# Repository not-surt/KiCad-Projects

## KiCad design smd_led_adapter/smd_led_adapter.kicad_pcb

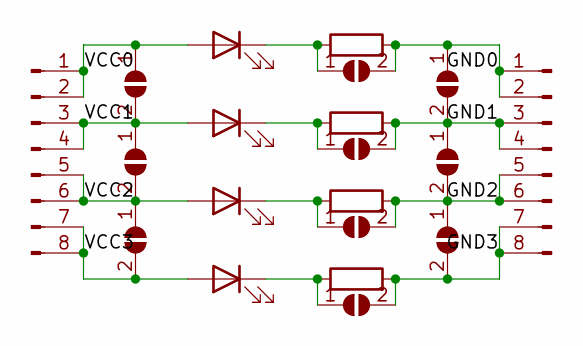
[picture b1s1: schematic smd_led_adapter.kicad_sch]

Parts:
D1, D2, D3, D4: LED; 1210_to_0603_combo_HandSolder
J1, J2: Conn_01x08_Male; PinHeader_1x08_P2.54mm_Vertical
JP1, JP2, JP3, JP4, JP5, JP6, JP7, JP8, JP9, JP10: SolderJumper_2_Open; SolderJumper-2_P1.3mm_Open_RoundedPad1.0x1.5mm
R1, R2, R3, R4: R; R_1206_3216Metric_Pad1.30x1.75mm_HandSolder

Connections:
/GND0: J2.1, J2.2, JP4.2 (B), JP8.1 (A), R1.2
/GND1: J2.3, J2.4, JP5.2 (B), JP8.2 (B), JP9.1 (A), R2.2
/GND2: J2.5, J2.6, JP6.2 (B), JP9.2 (B), JP10.1 (A), R3.2
/GND3: J2.7, J2.8, JP7.2 (B), JP10.2 (B), R4.2
/VCC0: D1.2 (A), J1.1, J1.2, JP1.1 (A)
/VCC1: D2.2 (A), J1.3, J1.4, JP1.2 (B), JP2.1 (A)
/VCC2: D3.2 (A), J1.5, J1.6, JP2.2 (B), JP3.1 (A)
/VCC3: D4.2 (A), J1.7, J1.8, JP3.2 (B)
unnamed: D1.1 (K), JP4.1 (A), R1.1
unnamed: D2.1 (K), JP5.1 (A), R2.1
unnamed: D3.1 (K), JP6.1 (A), R3.1
unnamed: D4.1 (K), JP7.1 (A), R4.1

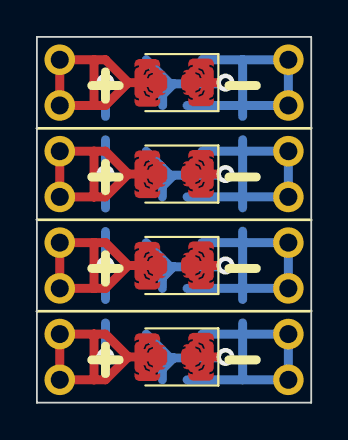
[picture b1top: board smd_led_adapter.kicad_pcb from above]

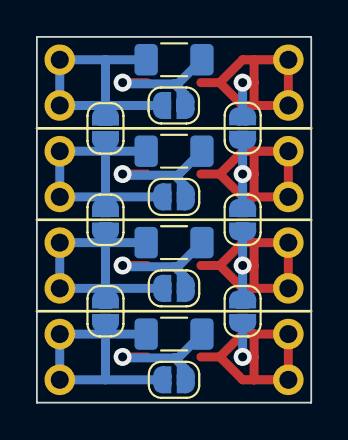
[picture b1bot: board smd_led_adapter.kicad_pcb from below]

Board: 2 copper layers, 15.2 x 20.3 mm, 20 parts (16 on the bottom side), 12 nets.

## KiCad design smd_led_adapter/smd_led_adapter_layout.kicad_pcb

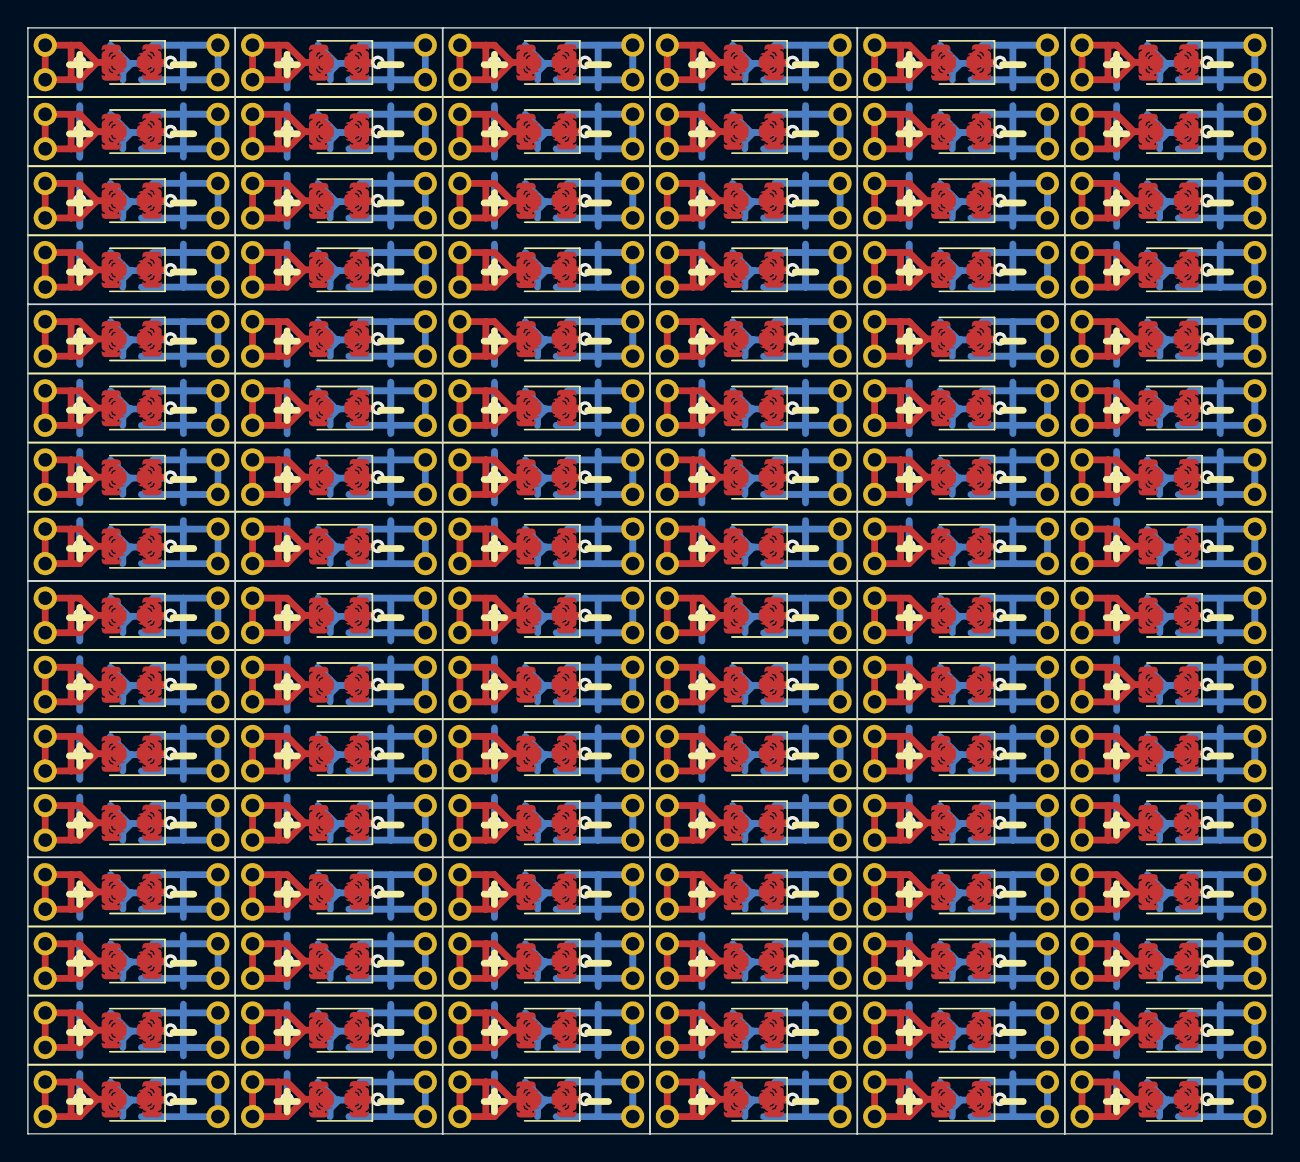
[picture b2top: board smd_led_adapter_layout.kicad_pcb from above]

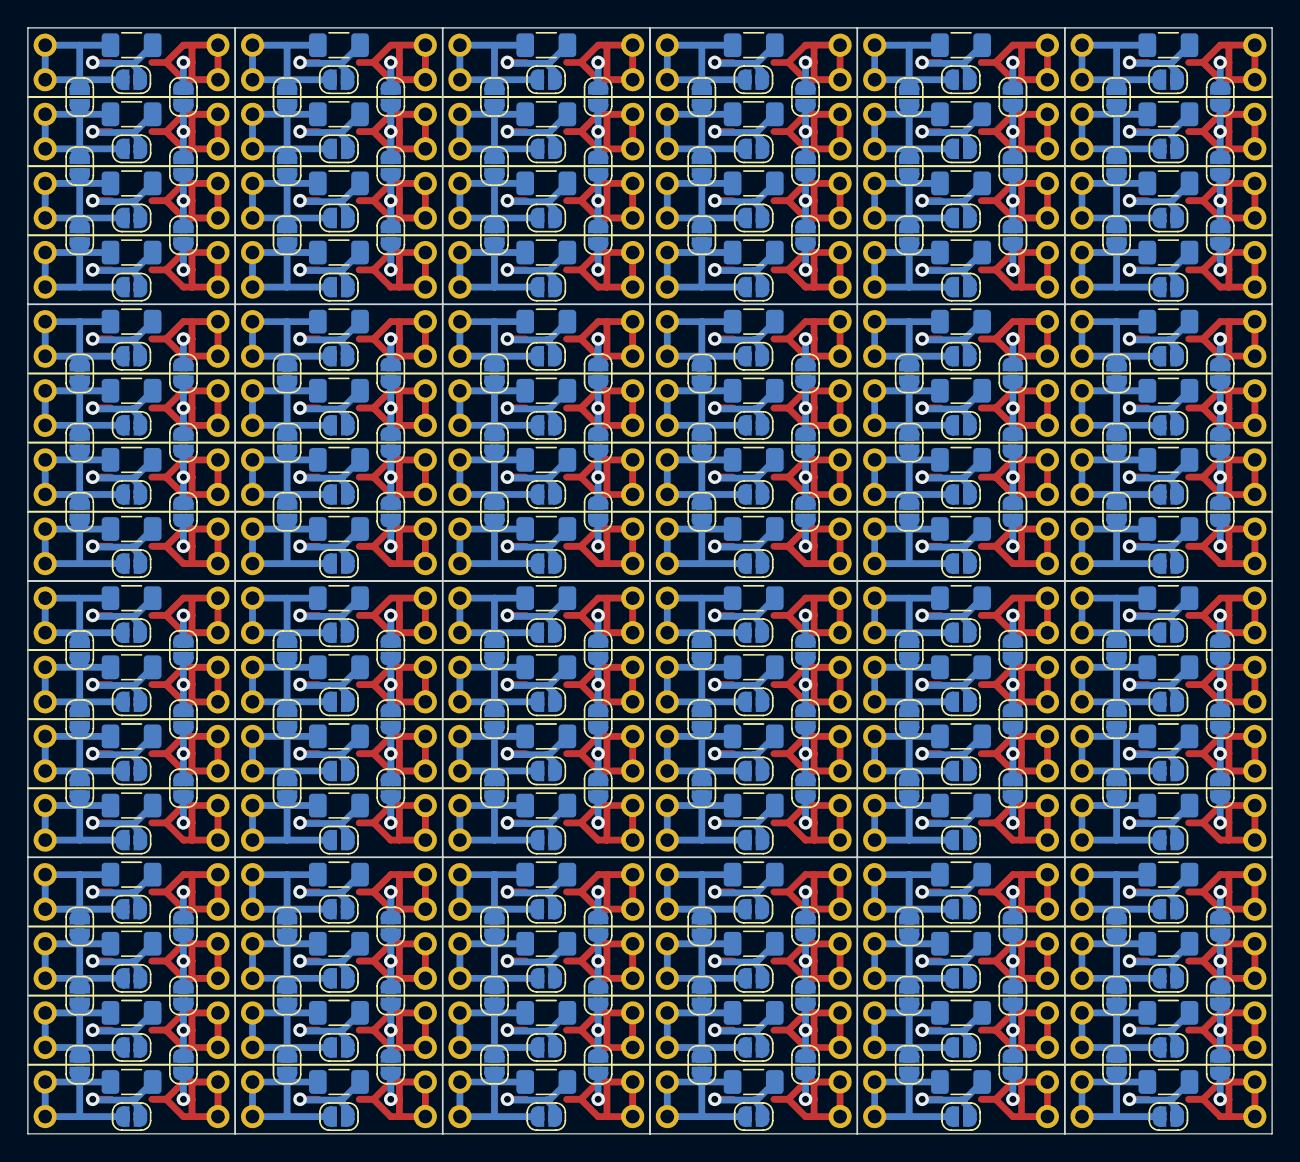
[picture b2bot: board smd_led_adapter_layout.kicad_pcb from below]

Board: 2 copper layers, 91.4 x 81.3 mm, 480 parts (384 on the bottom side), 12 nets.

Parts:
D1, D2, D3, D4, D5, D6, D7, D8, D9, D10, D11, D12, D13, D14, D15, D16, D17, D18, D19, D20, D21, D22, D23, D24, D25, D26, D27, D28, D29, D30, D31, D32, D33, D34, D35, D36, D37, D38, D39, D40, D41, D42, D43, D44, D45, D46, D47, D48, D49, D50, D51, D52, D53, D54, D55, D56, D57, D58, D59, D60, D61, D62, D63, D64, D65, D66, D67, D68, D69, D70, D71, D72, D73, D74, D75, D76, D77, D78, D79, D80, D81, D82, D83, D84, D85, D86, D87, D88, D89, D90, D91, D92, D93, D94, D95, D96: LED; 1210_to_0603_combo_HandSolder
J1, J2, J3, J4, J5, J6, J7, J8, J9, J10, J11, J12, J13, J14, J15, J16, J17, J18, J19, J20, J21, J22, J23, J24, J25, J26, J27, J28, J29, J30, J31, J32, J33, J34, J35, J36, J37, J38, J39, J40, J41, J42, J43, J44, J45, J46, J47, J48: Conn_01x08_Male; PinHeader_1x08_P2.54mm_Vertical
JP1, JP2, JP3, JP4, JP5, JP6, JP7, JP8, JP9, JP10, JP11, JP12, JP13, JP14, JP15, JP16, JP17, JP18, JP19, JP20, JP21, JP22, JP23, JP24, JP25, JP26, JP27, JP28, JP29, JP30, JP31, JP32, JP33, JP34, JP35, JP36, JP37, JP38, JP39, JP40, JP41, JP42, JP43, JP44, JP45, JP46, JP47, JP48, JP49, JP50, JP51, JP52, JP53, JP54, JP55, JP56, JP57, JP58, JP59, JP60, JP61, JP62, JP63, JP64, JP65, JP66, JP67, JP68, JP69, JP70, JP71, JP72, JP73, JP74, JP75, JP76, JP77, JP78, JP79, JP80, JP81, JP82, JP83, JP84, JP85, JP86, JP87, JP88, JP89, JP90, JP91, JP92, JP93, JP94, JP95, JP96, JP97, JP98, JP99, JP100, JP101, JP102, JP103, JP104, JP105, JP106, JP107, JP108, JP109, JP110, JP111, JP112, JP113, JP114, JP115, JP116, JP117, JP118, JP119, JP120, JP121, JP122, JP123, JP124, JP125, JP126, JP127, JP128, JP129, JP130, JP131, JP132, JP133, JP134, JP135, JP136, JP137, JP138, JP139, JP140, JP141, JP142, JP143, JP144, JP145, JP146, JP147, JP148, JP149, JP150, JP151, JP152, JP153, JP154, JP155, JP156, JP157, JP158, JP159, JP160, JP161, JP162, JP163, JP164, JP165, JP166, JP167, JP168, JP169, JP170, JP171, JP172, JP173, JP174, JP175, JP176, JP177, JP178, JP179, JP180, JP181, JP182, JP183, JP184, JP185, JP186, JP187, JP188, JP189, JP190, JP191, JP192, JP193, JP194, JP195, JP196, JP197, JP198, JP199, JP200, JP201, JP202, JP203, JP204, JP205, JP206, JP207, JP208, JP209, JP210, JP211, JP212, JP213, JP214, JP215, JP216, JP217, JP218, JP219, JP220, JP221, JP222, JP223, JP224, JP225, JP226, JP227, JP228, JP229, JP230, JP231, JP232, JP233, JP234, JP235, JP236, JP237, JP238, JP239, JP240: SolderJumper_2_Open; SolderJumper-2_P1.3mm_Open_RoundedPad1.0x1.5mm
R1, R2, R3, R4, R5, R6, R7, R8, R9, R10, R11, R12, R13, R14, R15, R16, R17, R18, R19, R20, R21, R22, R23, R24, R25, R26, R27, R28, R29, R30, R31, R32, R33, R34, R35, R36, R37, R38, R39, R40, R41, R42, R43, R44, R45, R46, R47, R48, R49, R50, R51, R52, R53, R54, R55, R56, R57, R58, R59, R60, R61, R62, R63, R64, R65, R66, R67, R68, R69, R70, R71, R72, R73, R74, R75, R76, R77, R78, R79, R80, R81, R82, R83, R84, R85, R86, R87, R88, R89, R90, R91, R92, R93, R94, R95, R96: R; R_1206_3216Metric_Pad1.30x1.75mm_HandSolder

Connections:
/GND0: J2.1, J2.2, J4.1, J4.2, J6.1, J6.2, J8.1, J8.2, J10.1, J10.2, J12.1, J12.2, J14.1, J14.2, J16.1, J16.2, J18.1, J18.2, J20.1, J20.2, J22.1, J22.2, J24.1, J24.2, J26.1, J26.2, J28.1, J28.2, J30.1, J30.2, J32.1, J32.2, J34.1, J34.2, J36.1, J36.2, J38.1, J38.2, J40.1, J40.2, J42.1, J42.2, J44.1, J44.2, J46.1, J46.2, J48.1, J48.2, JP4.2 (B), JP8.1 (A), JP14.2 (B), JP18.1 (A), JP24.2 (B), JP28.1 (A), JP34.2 (B), JP38.1 (A), JP44.2 (B), JP48.1 (A), JP54.2 (B), JP58.1 (A), JP64.2 (B), JP68.1 (A), JP74.2 (B), JP78.1 (A), JP84.2 (B), JP88.1 (A), JP94.2 (B), JP98.1 (A), JP104.2 (B), JP108.1 (A), JP114.2 (B), JP118.1 (A), JP124.2 (B), JP128.1 (A), JP134.2 (B), JP138.1 (A), JP144.2 (B), JP148.1 (A), JP154.2 (B), JP158.1 (A), JP164.2 (B), JP168.1 (A), JP174.2 (B), JP178.1 (A), JP184.2 (B), JP188.1 (A), JP194.2 (B), JP198.1 (A), JP204.2 (B), JP208.1 (A), JP214.2 (B), JP218.1 (A), JP224.2 (B), JP228.1 (A), JP234.2 (B), JP238.1 (A), R1.2, R5.2, R9.2, R13.2, R17.2, R21.2, R25.2, R29.2, R33.2, R37.2, R41.2, R45.2, R49.2, R53.2, R57.2, R61.2, R65.2, R69.2, R73.2, R77.2, R81.2, R85.2, R89.2, R93.2
/GND1: J2.3, J2.4, J4.3, J4.4, J6.3, J6.4, J8.3, J8.4, J10.3, J10.4, J12.3, J12.4, J14.3, J14.4, J16.3, J16.4, J18.3, J18.4, J20.3, J20.4, J22.3, J22.4, J24.3, J24.4, J26.3, J26.4, J28.3, J28.4, J30.3, J30.4, J32.3, J32.4, J34.3, J34.4, J36.3, J36.4, J38.3, J38.4, J40.3, J40.4, J42.3, J42.4, J44.3, J44.4, J46.3, J46.4, J48.3, J48.4, JP5.2 (B), JP8.2 (B), JP9.1 (A), JP15.2 (B), JP18.2 (B), JP19.1 (A), JP25.2 (B), JP28.2 (B), JP29.1 (A), JP35.2 (B), JP38.2 (B), JP39.1 (A), JP45.2 (B), JP48.2 (B), JP49.1 (A), JP55.2 (B), JP58.2 (B), JP59.1 (A), JP65.2 (B), JP68.2 (B), JP69.1 (A), JP75.2 (B), JP78.2 (B), JP79.1 (A), JP85.2 (B), JP88.2 (B), JP89.1 (A), JP95.2 (B), JP98.2 (B), JP99.1 (A), JP105.2 (B), JP108.2 (B), JP109.1 (A), JP115.2 (B), JP118.2 (B), JP119.1 (A), JP125.2 (B), JP128.2 (B), JP129.1 (A), JP135.2 (B), JP138.2 (B), JP139.1 (A), JP145.2 (B), JP148.2 (B), JP149.1 (A), JP155.2 (B), JP158.2 (B), JP159.1 (A), JP165.2 (B), JP168.2 (B), JP169.1 (A), JP175.2 (B), JP178.2 (B), JP179.1 (A), JP185.2 (B), JP188.2 (B), JP189.1 (A), JP195.2 (B), JP198.2 (B), JP199.1 (A), JP205.2 (B), JP208.2 (B), JP209.1 (A), JP215.2 (B), JP218.2 (B), JP219.1 (A), JP225.2 (B), JP228.2 (B), JP229.1 (A), JP235.2 (B), JP238.2 (B), JP239.1 (A), R2.2, R6.2, R10.2, R14.2, R18.2, R22.2, R26.2, R30.2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
/GND2: J2.5, J2.6, J4.5, J4.6, J6.5, J6.6, J8.5, J8.6, J10.5, J10.6, J12.5, J12.6, J14.5, J14.6, J16.5, J16.6, J18.5, J18.6, J20.5, J20.6, J22.5, J22.6, J24.5, J24.6, J26.5, J26.6, J28.5, J28.6, J30.5, J30.6, J32.5, J32.6, J34.5, J34.6, J36.5, J36.6, J38.5, J38.6, J40.5, J40.6, J42.5, J42.6, J44.5, J44.6, J46.5, J46.6, J48.5, J48.6, JP6.2 (B), JP9.2 (B), JP10.1 (A), JP16.2 (B), JP19.2 (B), JP20.1 (A), JP26.2 (B), JP29.2 (B), JP30.1 (A), JP36.2 (B), JP39.2 (B), JP40.1 (A), JP46.2 (B), JP49.2 (B), JP50.1 (A), JP56.2 (B), JP59.2 (B), JP60.1 (A), JP66.2 (B), JP69.2 (B), JP70.1 (A), JP76.2 (B), JP79.2 (B), JP80.1 (A), JP86.2 (B), JP89.2 (B), JP90.1 (A), JP96.2 (B), JP99.2 (B), JP100.1 (A), JP106.2 (B), JP109.2 (B), JP110.1 (A), JP116.2 (B), JP119.2 (B), JP120.1 (A), JP126.2 (B), JP129.2 (B), JP130.1 (A), JP136.2 (B), JP139.2 (B), JP140.1 (A), JP146.2 (B), JP149.2 (B), JP150.1 (A), JP156.2 (B), JP159.2 (B), JP160.1 (A), JP166.2 (B), JP169.2 (B), JP170.1 (A), JP176.2 (B), JP179.2 (B), JP180.1 (A), JP186.2 (B), JP189.2 (B), JP190.1 (A), JP196.2 (B), JP199.2 (B), JP200.1 (A), JP206.2 (B), JP209.2 (B), JP210.1 (A), JP216.2 (B), JP219.2 (B), JP220.1 (A), JP226.2 (B), JP229.2 (B), JP230.1 (A), JP236.2 (B), JP239.2 (B), JP240.1 (A), R3.2, R7.2, R11.2, R15.2, R19.2, R23.2, R27.2, R31.2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
/GND3: J2.7, J2.8, J4.7, J4.8, J6.7, J6.8, J8.7, J8.8, J10.7, J10.8, J12.7, J12.8, J14.7, J14.8, J16.7, J16.8, J18.7, J18.8, J20.7, J20.8, J22.7, J22.8, J24.7, J24.8, J26.7, J26.8, J28.7, J28.8, J30.7, J30.8, J32.7, J32.8, J34.7, J34.8, J36.7, J36.8, J38.7, J38.8, J40.7, J40.8, J42.7, J42.8, J44.7, J44.8, J46.7, J46.8, J48.7, J48.8, JP7.2 (B), JP10.2 (B), JP17.2 (B), JP20.2 (B), JP27.2 (B), JP30.2 (B), JP37.2 (B), JP40.2 (B), JP47.2 (B), JP50.2 (B), JP57.2 (B), JP60.2 (B), JP67.2 (B), JP70.2 (B), JP77.2 (B), JP80.2 (B), JP87.2 (B), JP90.2 (B), JP97.2 (B), JP100.2 (B), JP107.2 (B), JP110.2 (B), JP117.2 (B), JP120.2 (B), JP127.2 (B), JP130.2 (B), JP137.2 (B), JP140.2 (B), JP147.2 (B), JP150.2 (B), JP157.2 (B), JP160.2 (B), JP167.2 (B), JP170.2 (B), JP177.2 (B), JP180.2 (B), JP187.2 (B), JP190.2 (B), JP197.2 (B), JP200.2 (B), JP207.2 (B), JP210.2 (B), JP217.2 (B), JP220.2 (B), JP227.2 (B), JP230.2 (B), JP237.2 (B), JP240.2 (B), R4.2, R8.2, R12.2, R16.2, R20.2, R24.2, R28.2, R32.2, R36.2, R40.2, R44.2, R48.2, R52.2, R56.2, R60.2, R64.2, R68.2, R72.2, R76.2, R80.2, R84.2, R88.2, R92.2, R96.2
/VCC0: D1.2 (A), D5.2 (A), D9.2 (A), D13.2 (A), D17.2 (A), D21.2 (A), D25.2 (A), D29.2 (A), D33.2 (A), D37.2 (A), D41.2 (A), D45.2 (A), D49.2 (A), D53.2 (A), D57.2 (A), D61.2 (A), D65.2 (A), D69.2 (A), D73.2 (A), D77.2 (A), D81.2 (A), D85.2 (A), D89.2 (A), D93.2 (A), J1.1, J1.2, J3.1, J3.2, J5.1, J5.2, J7.1, J7.2, J9.1, J9.2, J11.1, J11.2, J13.1, J13.2, J15.1, J15.2, J17.1, J17.2, J19.1, J19.2, J21.1, J21.2, J23.1, J23.2, J25.1, J25.2, J27.1, J27.2, J29.1, J29.2, J31.1, J31.2, J33.1, J33.2, J35.1, J35.2, J37.1, J37.2, J39.1, J39.2, J41.1, J41.2, J43.1, J43.2, J45.1, J45.2, J47.1, J47.2, JP1.1 (A), JP11.1 (A), JP21.1 (A), JP31.1 (A), JP41.1 (A), JP51.1 (A), JP61.1 (A), JP71.1 (A), JP81.1 (A), JP91.1 (A), JP101.1 (A), JP111.1 (A), JP121.1 (A), JP131.1 (A), JP141.1 (A), JP151.1 (A), JP161.1 (A), JP171.1 (A), JP181.1 (A), JP191.1 (A), JP201.1 (A), JP211.1 (A), JP221.1 (A), JP231.1 (A)
/VCC1: D2.2 (A), D6.2 (A), D10.2 (A), D14.2 (A), D18.2 (A), D22.2 (A), D26.2 (A), D30.2 (A), D34.2 (A), D38.2 (A), D42.2 (A), D46.2 (A), D50.2 (A), D54.2 (A), D58.2 (A), D62.2 (A), D66.2 (A), D70.2 (A), D74.2 (A), D78.2 (A), D82.2 (A), D86.2 (A), D90.2 (A), D94.2 (A), J1.3, J1.4, J3.3, J3.4, J5.3, J5.4, J7.3, J7.4, J9.3, J9.4, J11.3, J11.4, J13.3, J13.4, J15.3, J15.4, J17.3, J17.4, J19.3, J19.4, J21.3, J21.4, J23.3, J23.4, J25.3, J25.4, J27.3, J27.4, J29.3, J29.4, J31.3, J31.4, J33.3, J33.4, J35.3, J35.4, J37.3, J37.4, J39.3, J39.4, J41.3, J41.4, J43.3, J43.4, J45.3, J45.4, J47.3, J47.4, JP1.2 (B), JP2.1 (A), JP11.2 (B), JP12.1 (A), JP21.2 (B), JP22.1 (A), JP31.2 (B), JP32.1 (A), JP41.2 (B), JP42.1 (A), JP51.2 (B), JP52.1 (A), JP61.2 (B), JP62.1 (A), JP71.2 (B), JP72.1 (A), JP81.2 (B), JP82.1 (A), JP91.2 (B), JP92.1 (A), JP101.2 (B), JP102.1 (A), JP111.2 (B), JP112.1 (A), JP121.2 (B), JP122.1 (A), JP131.2 (B), JP132.1 (A), JP141.2 (B), JP142.1 (A), JP151.2 (B), JP152.1 (A), JP161.2 (B), JP162.1 (A), JP171.2 (B), JP172.1 (A), JP181.2 (B), JP182.1 (A), JP191.2 (B), JP192.1 (A), JP201.2 (B), JP202.1 (A), JP211.2 (B), JP212.1 (A), JP221.2 (B), JP222.1 (A), JP231.2 (B), JP232.1 (A)
/VCC2: D3.2 (A), D7.2 (A), D11.2 (A), D15.2 (A), D19.2 (A), D23.2 (A), D27.2 (A), D31.2 (A), D35.2 (A), D39.2 (A), D43.2 (A), D47.2 (A), D51.2 (A), D55.2 (A), D59.2 (A), D63.2 (A), D67.2 (A), D71.2 (A), D75.2 (A), D79.2 (A), D83.2 (A), D87.2 (A), D91.2 (A), D95.2 (A), J1.5, J1.6, J3.5, J3.6, J5.5, J5.6, J7.5, J7.6, J9.5, J9.6, J11.5, J11.6, J13.5, J13.6, J15.5, J15.6, J17.5, J17.6, J19.5, J19.6, J21.5, J21.6, J23.5, J23.6, J25.5, J25.6, J27.5, J27.6, J29.5, J29.6, J31.5, J31.6, J33.5, J33.6, J35.5, J35.6, J37.5, J37.6, J39.5, J39.6, J41.5, J41.6, J43.5, J43.6, J45.5, J45.6, J47.5, J47.6, JP2.2 (B), JP3.1 (A), JP12.2 (B), JP13.1 (A), JP22.2 (B), JP23.1 (A), JP32.2 (B), JP33.1 (A), JP42.2 (B), JP43.1 (A), JP52.2 (B), JP53.1 (A), JP62.2 (B), JP63.1 (A), JP72.2 (B), JP73.1 (A), JP82.2 (B), JP83.1 (A), JP92.2 (B), JP93.1 (A), JP102.2 (B), JP103.1 (A), JP112.2 (B), JP113.1 (A), JP122.2 (B), JP123.1 (A), JP132.2 (B), JP133.1 (A), JP142.2 (B), JP143.1 (A), JP152.2 (B), JP153.1 (A), JP162.2 (B), JP163.1 (A), JP172.2 (B), JP173.1 (A), JP182.2 (B), JP183.1 (A), JP192.2 (B), JP193.1 (A), JP202.2 (B), JP203.1 (A), JP212.2 (B), JP213.1 (A), JP222.2 (B), JP223.1 (A), JP232.2 (B), JP233.1 (A)
/VCC3: D4.2 (A), D8.2 (A), D12.2 (A), D16.2 (A), D20.2 (A), D24.2 (A), D28.2 (A), D32.2 (A), D36.2 (A), D40.2 (A), D44.2 (A), D48.2 (A), D52.2 (A), D56.2 (A), D60.2 (A), D64.2 (A), D68.2 (A), D72.2 (A), D76.2 (A), D80.2 (A), D84.2 (A), D88.2 (A), D92.2 (A), D96.2 (A), J1.7, J1.8, J3.7, J3.8, J5.7, J5.8, J7.7, J7.8, J9.7, J9.8, J11.7, J11.8, J13.7, J13.8, J15.7, J15.8, J17.7, J17.8, J19.7, J19.8, J21.7, J21.8, J23.7, J23.8, J25.7, J25.8, J27.7, J27.8, J29.7, J29.8, J31.7, J31.8, J33.7, J33.8, J35.7, J35.8, J37.7, J37.8, J39.7, J39.8, J41.7, J41.8, J43.7, J43.8, J45.7, J45.8, J47.7, J47.8, JP3.2 (B), JP13.2 (B), JP23.2 (B), JP33.2 (B), JP43.2 (B), JP53.2 (B), JP63.2 (B), JP73.2 (B), JP83.2 (B), JP93.2 (B), JP103.2 (B), JP113.2 (B), JP123.2 (B), JP133.2 (B), JP143.2 (B), JP153.2 (B), JP163.2 (B), JP173.2 (B), JP183.2 (B), JP193.2 (B), JP203.2 (B), JP213.2 (B), JP223.2 (B), JP233.2 (B)
unnamed: D1.1 (K), D5.1 (K), D9.1 (K), D13.1 (K), D17.1 (K), D21.1 (K), D25.1 (K), D29.1 (K), D33.1 (K), D37.1 (K), D41.1 (K), D45.1 (K), D49.1 (K), D53.1 (K), D57.1 (K), D61.1 (K), D65.1 (K), D69.1 (K), D73.1 (K), D77.1 (K), D81.1 (K), D85.1 (K), D89.1 (K), D93.1 (K), JP4.1 (A), JP14.1 (A), JP24.1 (A), JP34.1 (A), JP44.1 (A), JP54.1 (A), JP64.1 (A), JP74.1 (A), JP84.1 (A), JP94.1 (A), JP104.1 (A), JP114.1 (A), JP124.1 (A), JP134.1 (A), JP144.1 (A), JP154.1 (A), JP164.1 (A), JP174.1 (A), JP184.1 (A), JP194.1 (A), JP204.1 (A), JP214.1 (A), JP224.1 (A), JP234.1 (A), R1.1, R5.1, R9.1, R13.1, R17.1, R21.1, R25.1, R29.1, R33.1, R37.1, R41.1, R45.1, R49.1, R53.1, R57.1, R61.1, R65.1, R69.1, R73.1, R77.1, R81.1, R85.1, R89.1, R93.1
unnamed: D2.1 (K), D6.1 (K), D10.1 (K), D14.1 (K), D18.1 (K), D22.1 (K), D26.1 (K), D30.1 (K), D34.1 (K), D38.1 (K), D42.1 (K), D46.1 (K), D50.1 (K), D54.1 (K), D58.1 (K), D62.1 (K), D66.1 (K), D70.1 (K), D74.1 (K), D78.1 (K), D82.1 (K), D86.1 (K), D90.1 (K), D94.1 (K), JP5.1 (A), JP15.1 (A), JP25.1 (A), JP35.1 (A), JP45.1 (A), JP55.1 (A), JP65.1 (A), JP75.1 (A), JP85.1 (A), JP95.1 (A), JP105.1 (A), JP115.1 (A), JP125.1 (A), JP135.1 (A), JP145.1 (A), JP155.1 (A), JP165.1 (A), JP175.1 (A), JP185.1 (A), JP195.1 (A), JP205.1 (A), JP215.1 (A), JP225.1 (A), JP235.1 (A), R2.1, R6.1, R10.1, R14.1, R18.1, R22.1, R26.1, R30.1, R34.1, R38.1, R42.1, R46.1, R50.1, R54.1, R58.1, R62.1, R66.1, R70.1, R74.1, R78.1, R82.1, R86.1, R90.1, R94.1
unnamed: D3.1 (K), D7.1 (K), D11.1 (K), D15.1 (K), D19.1 (K), D23.1 (K), D27.1 (K), D31.1 (K), D35.1 (K), D39.1 (K), D43.1 (K), D47.1 (K), D51.1 (K), D55.1 (K), D59.1 (K), D63.1 (K), D67.1 (K), D71.1 (K), D75.1 (K), D79.1 (K), D83.1 (K), D87.1 (K), D91.1 (K), D95.1 (K), JP6.1 (A), JP16.1 (A), JP26.1 (A), JP36.1 (A), JP46.1 (A), JP56.1 (A), JP66.1 (A), JP76.1 (A), JP86.1 (A), JP96.1 (A), JP106.1 (A), JP116.1 (A), JP126.1 (A), JP136.1 (A), JP146.1 (A), JP156.1 (A), JP166.1 (A), JP176.1 (A), JP186.1 (A), JP196.1 (A), JP206.1 (A), JP216.1 (A), JP226.1 (A), JP236.1 (A), R3.1, R7.1, R11.1, R15.1, R19.1, R23.1, R27.1, R31.1, R35.1, R39.1, R43.1, R47.1, R51.1, R55.1, R59.1, R63.1, R67.1, R71.1, R75.1, R79.1, R83.1, R87.1, R91.1, R95.1
unnamed: D4.1 (K), D8.1 (K), D12.1 (K), D16.1 (K), D20.1 (K), D24.1 (K), D28.1 (K), D32.1 (K), D36.1 (K), D40.1 (K), D44.1 (K), D48.1 (K), D52.1 (K), D56.1 (K), D60.1 (K), D64.1 (K), D68.1 (K), D72.1 (K), D76.1 (K), D80.1 (K), D84.1 (K), D88.1 (K), D92.1 (K), D96.1 (K), JP7.1 (A), JP17.1 (A), JP27.1 (A), JP37.1 (A), JP47.1 (A), JP57.1 (A), JP67.1 (A), JP77.1 (A), JP87.1 (A), JP97.1 (A), JP107.1 (A), JP117.1 (A), JP127.1 (A), JP137.1 (A), JP147.1 (A), JP157.1 (A), JP167.1 (A), JP177.1 (A), JP187.1 (A), JP197.1 (A), JP207.1 (A), JP217.1 (A), JP227.1 (A), JP237.1 (A), R4.1, R8.1, R12.1, R16.1, R20.1, R24.1, R28.1, R32.1, R36.1, R40.1, R44.1, R48.1, R52.1, R56.1, R60.1, R64.1, R68.1, R72.1, R76.1, R80.1, R84.1, R88.1, R92.1, R96.1

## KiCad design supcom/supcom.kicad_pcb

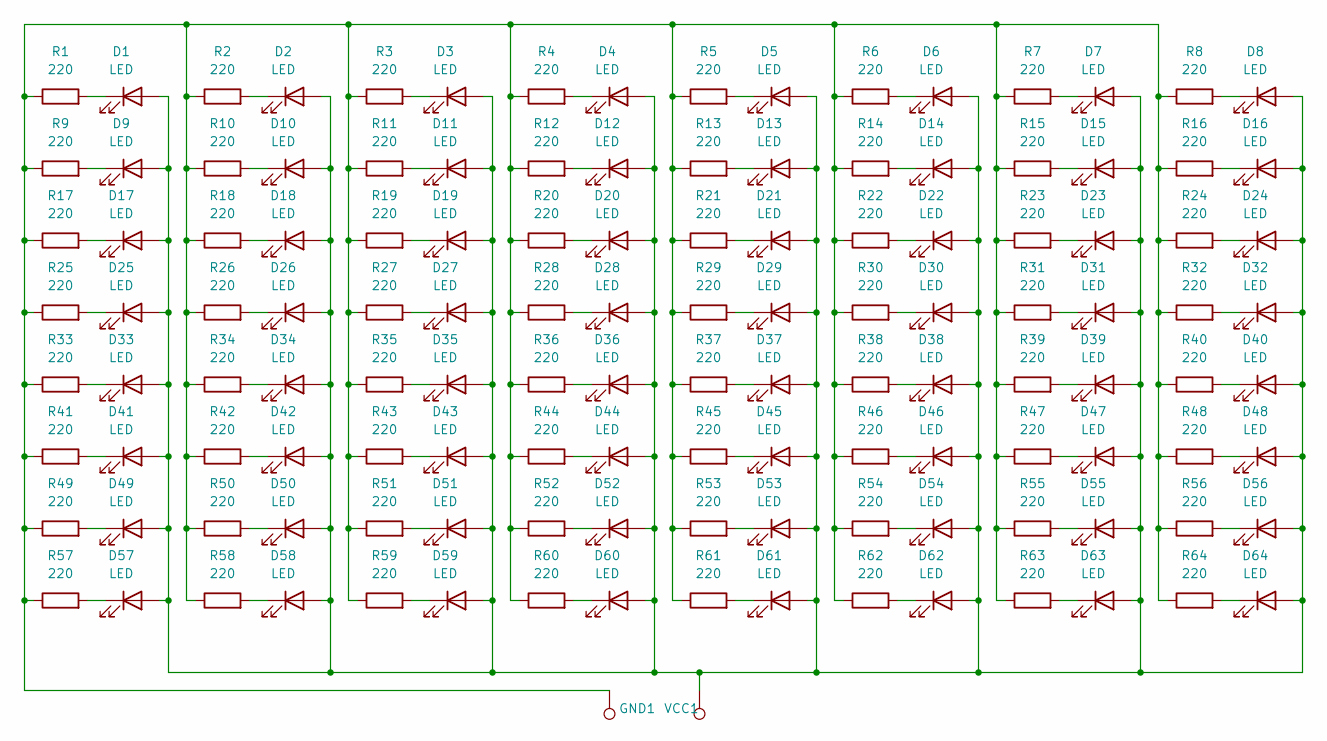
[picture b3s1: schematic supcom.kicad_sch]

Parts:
D1, D2, D3, D4, D5, D6, D7, D8, D9, D10, D11, D12, D13, D14, D15, D16, D17, D18, D19, D20, D21, D22, D23, D24, D25, D26, D27, D28, D29, D30, D31, D32, D33, D34, D35, D36, D37, D38, D39, D40, D41, D42, D43, D44, D45, D46, D47, D48, D49, D50, D51, D52, D53, D54, D55, D56, D57, D58, D59, D60, D61, D62, D63, D64: LED; LED_D5.0mm
GND1: (no value)
R1, R2, R3, R4, R5, R6, R7, R8, R9, R10, R11, R12, R13, R14, R15, R16, R17, R18, R19, R20, R21, R22, R23, R24, R25, R26, R27, R28, R29, R30, R31, R32, R33, R34, R35, R36, R37, R38, R39, R40, R41, R42, R43, R44, R45, R46, R47, R48, R49, R50, R51, R52, R53, R54, R55, R56, R57, R58, R59, R60, R61, R62, R63, R64: 220; R_Axial_DIN0207_L6.3mm_D2.5mm_P7.62mm_Horizontal
VCC1: (no value)

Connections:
unnamed: D1.1 (K), R1.2
unnamed: D1.2 (A), D2.2 (A), D3.2 (A), D4.2 (A), D5.2 (A), D6.2 (A), D7.2 (A), D8.2 (A), D9.2 (A), D10.2 (A), D11.2 (A), D12.2 (A), D13.2 (A), D14.2 (A), D15.2 (A), D16.2 (A), D17.2 (A), D18.2 (A), D19.2 (A), D20.2 (A), D21.2 (A), D22.2 (A), D23.2 (A), D24.2 (A), D25.2 (A), D26.2 (A), D27.2 (A), D28.2 (A), D29.2 (A), D30.2 (A), D31.2 (A), D32.2 (A), D33.2 (A), D34.2 (A), D35.2 (A), D36.2 (A), D37.2 (A), D38.2 (A), D39.2 (A), D40.2 (A), D41.2 (A), D42.2 (A), D43.2 (A), D44.2 (A), D45.2 (A), D46.2 (A), D47.2 (A), D48.2 (A), D49.2 (A), D50.2 (A), D51.2 (A), D52.2 (A), D53.2 (A), D54.2 (A), D55.2 (A), D56.2 (A), D57.2 (A), D58.2 (A), D59.2 (A), D60.2 (A), D61.2 (A), D62.2 (A), D63.2 (A), D64.2 (A), VCC1.1
unnamed: D2.1 (K), R2.2
unnamed: D3.1 (K), R3.2
unnamed: D4.1 (K), R4.2
unnamed: D5.1 (K), R5.2
unnamed: D6.1 (K), R6.2
unnamed: D7.1 (K), R7.2
unnamed: D8.1 (K), R8.2
unnamed: D9.1 (K), R9.2
unnamed: D10.1 (K), R10.2
unnamed: D11.1 (K), R11.2
unnamed: D12.1 (K), R12.2
unnamed: D13.1 (K), R13.2
unnamed: D14.1 (K), R14.2
unnamed: D15.1 (K), R15.2
unnamed: D16.1 (K), R16.2
unnamed: D17.1 (K), R17.2
unnamed: D18.1 (K), R18.2
unnamed: D19.1 (K), R19.2
unnamed: D20.1 (K), R20.2
unnamed: D21.1 (K), R21.2
unnamed: D22.1 (K), R22.2
unnamed: D23.1 (K), R23.2
unnamed: D24.1 (K), R24.2
unnamed: D25.1 (K), R25.2
unnamed: D26.1 (K), R26.2
unnamed: D27.1 (K), R27.2
unnamed: D28.1 (K), R28.2
unnamed: D29.1 (K), R29.2
unnamed: D30.1 (K), R30.2
unnamed: D31.1 (K), R31.2
unnamed: D32.1 (K), R32.2
unnamed: D33.1 (K), R33.2
unnamed: D34.1 (K), R34.2
unnamed: D35.1 (K), R35.2
unnamed: D36.1 (K), R36.2
unnamed: D37.1 (K), R37.2
unnamed: D38.1 (K), R38.2
unnamed: D39.1 (K), R39.2
unnamed: D40.1 (K), R40.2
unnamed: D41.1 (K), R41.2
unnamed: D42.1 (K), R42.2
unnamed: D43.1 (K), R43.2
unnamed: D44.1 (K), R44.2
unnamed: D45.1 (K), R45.2
unnamed: D46.1 (K), R46.2
unnamed: D47.1 (K), R47.2
unnamed: D48.1 (K), R48.2
unnamed: D49.1 (K), R49.2
unnamed: D50.1 (K), R50.2
unnamed: D51.1 (K), R51.2
unnamed: D52.1 (K), R52.2
unnamed: D53.1 (K), R53.2
unnamed: D54.1 (K), R54.2
unnamed: D55.1 (K), R55.2
unnamed: D56.1 (K), R56.2
unnamed: D57.1 (K), R57.2
unnamed: D58.1 (K), R58.2
unnamed: D59.1 (K), R59.2
unnamed: D60.1 (K), R60.2
unnamed: D61.1 (K), R61.2
unnamed: D62.1 (K), R62.2
unnamed: D63.1 (K), R63.2
unnamed: D64.1 (K), R64.2
unnamed: GND1.1, R1.1, R2.1, R3.1, R4.1, R5.1, R6.1, R7.1, R8.1, R9.1, R10.1, R11.1, R12.1, R13.1, R14.1, R15.1, R16.1, R17.1, R18.1, R19.1, R20.1, R21.1, R22.1, R23.1, R24.1, R25.1, R26.1, R27.1, R28.1, R29.1, R30.1, R31.1, R32.1, R33.1, R34.1, R35.1, R36.1, R37.1, R38.1, R39.1, R40.1, R41.1, R42.1, R43.1, R44.1, R45.1, R46.1, R47.1, R48.1, R49.1, R50.1, R51.1, R52.1, R53.1, R54.1, R55.1, R56.1, R57.1, R58.1, R59.1, R60.1, R61.1, R62.1, R63.1, R64.1

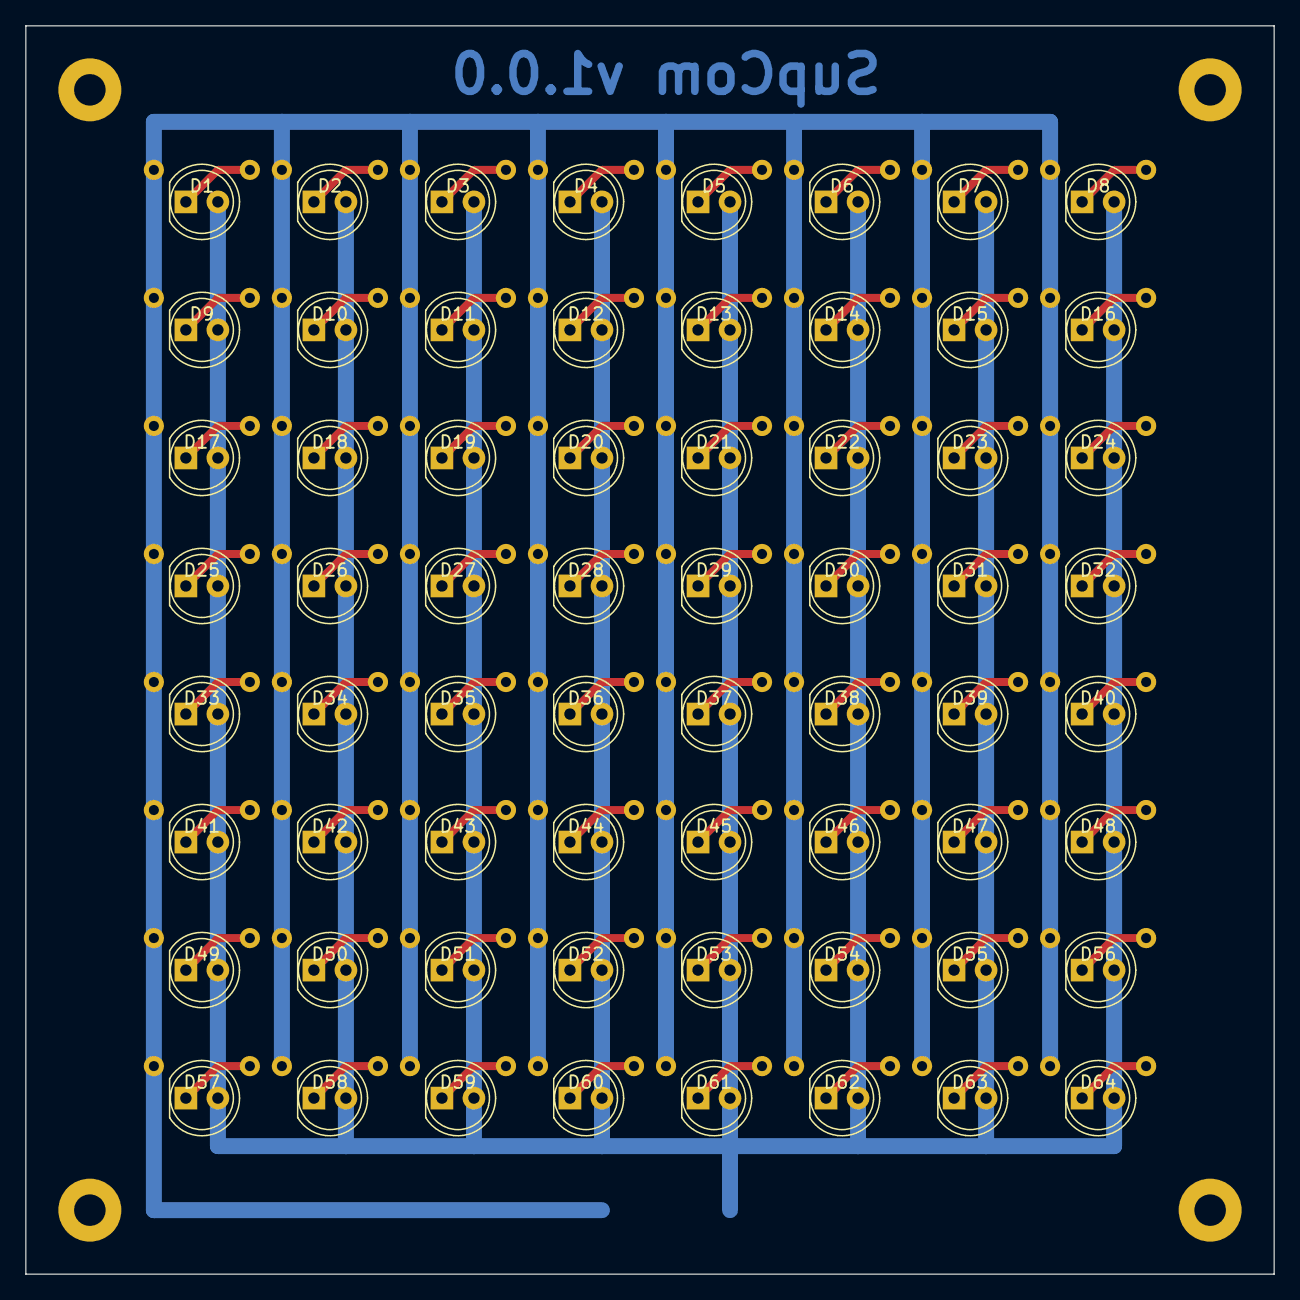
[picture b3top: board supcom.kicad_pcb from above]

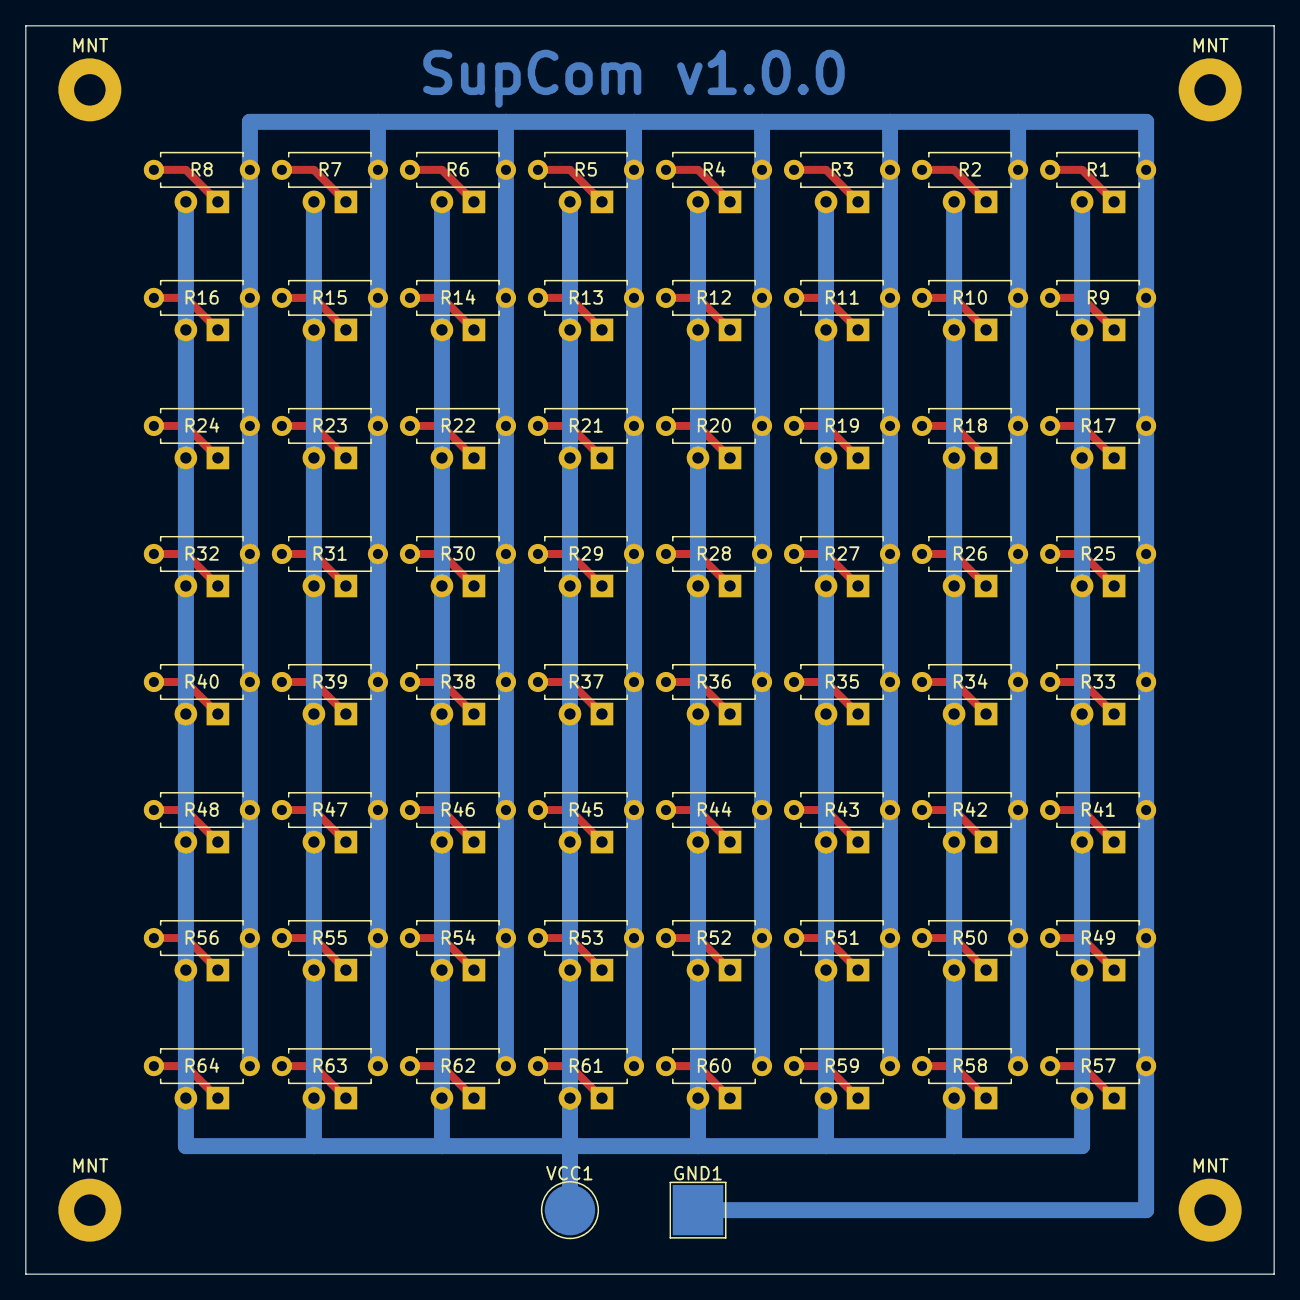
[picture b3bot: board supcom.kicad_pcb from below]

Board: 2 copper layers, 99.1 x 99.1 mm, 134 parts (70 on the bottom side), 66 nets.

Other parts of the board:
MNT: MountingHole_2.5mm_Pad
MNT#2, MNT#3, MNT#4: MountingHole_2.5mm_Pad

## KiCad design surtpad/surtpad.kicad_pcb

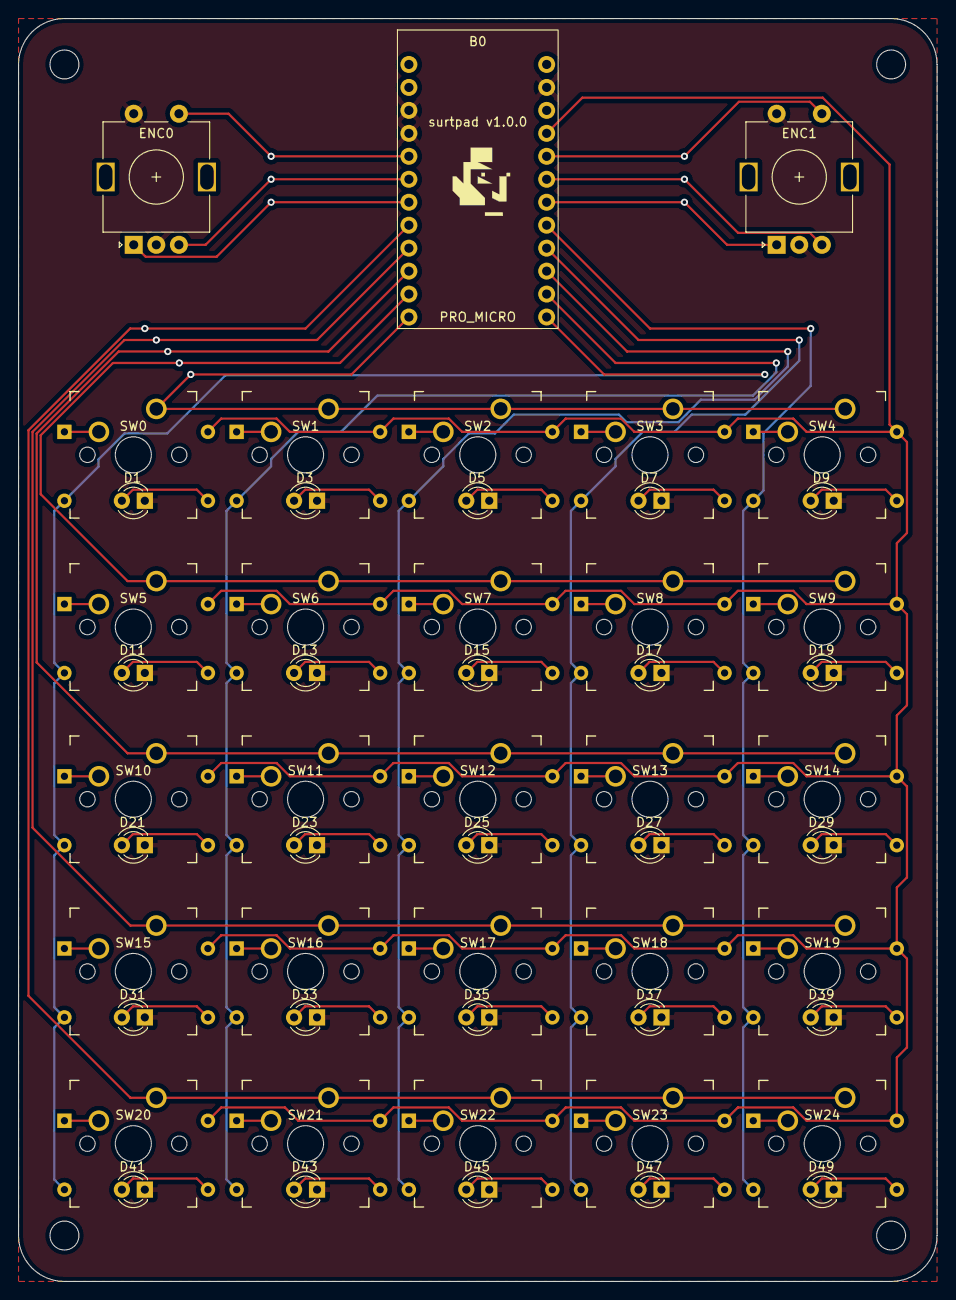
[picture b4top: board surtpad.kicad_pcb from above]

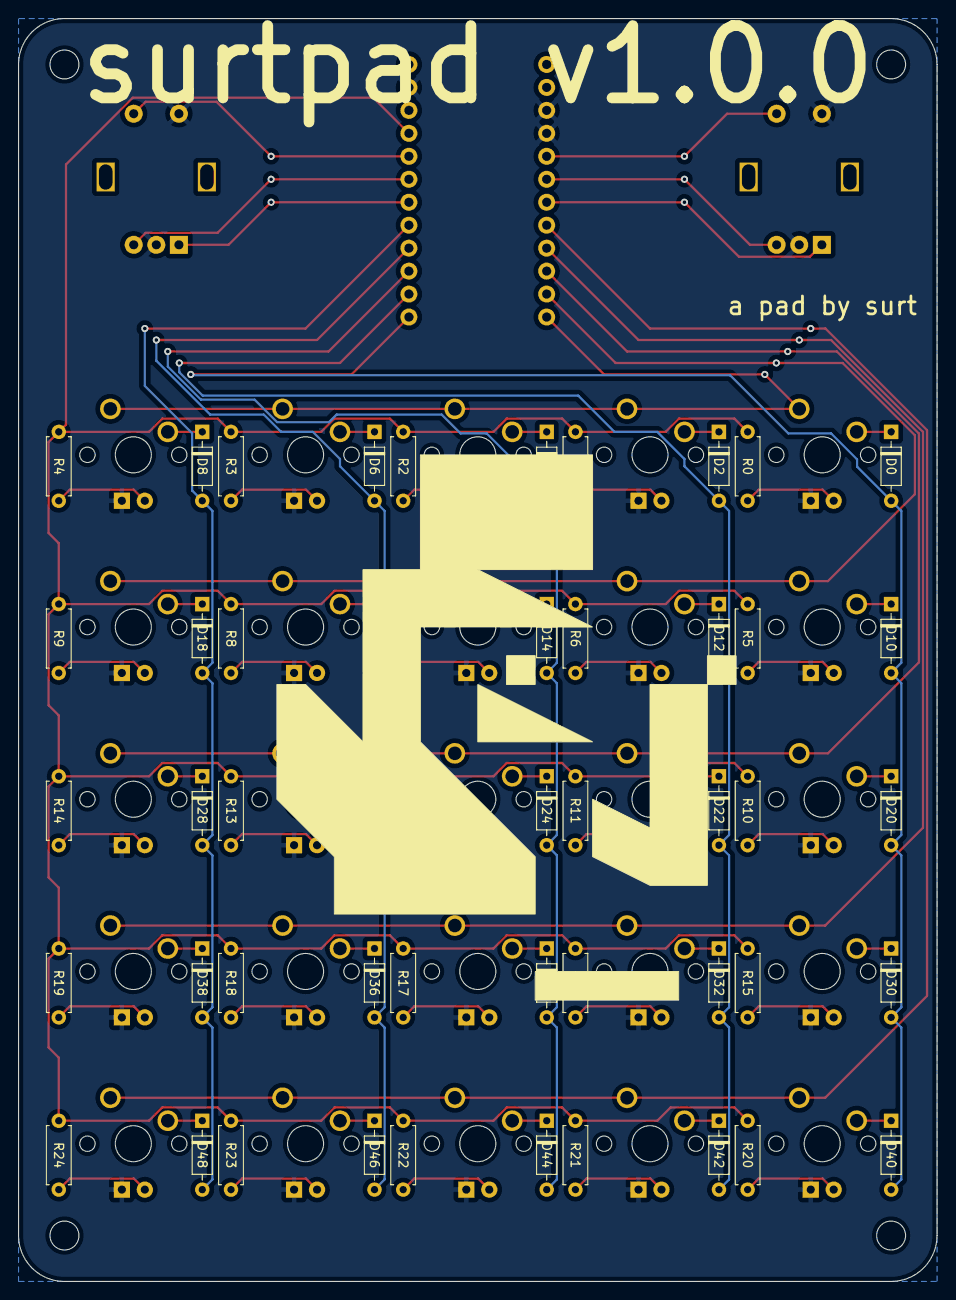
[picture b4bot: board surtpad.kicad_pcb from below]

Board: 2 copper layers, 101.6 x 139.7 mm, 103 parts (50 on the bottom side), 68 nets.

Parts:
B0: PRO_MICRO; SPARKFUN_PRO_MICRO
D0, D2, D4, D6, D8, D10, D12, D14, D16, D18, D20, D22, D24, D26, D28, D30, D32, D34, D36, D38, D40, D42, D44, D46, D48: D; D_DO-35_SOD27_P7.62mm_Horizontal
D1, D3, D5, D7, D9, D11, D13, D15, D17, D19, D21, D23, D25, D27, D29, D31, D33, D35, D37, D39, D41, D43, D45, D47, D49: LED; LED_D3.0mm
ENC0, ENC1: RotaryEncoder_Switch; RotaryEncoder_Alps_EC11E-Switch_Vertical_H20mm
R0, R1, R2, R3, R4, R5, R6, R7, R8, R9, R10, R11, R12, R13, R14, R15, R16, R17, R18, R19, R20, R21, R22, R23, R24: 220; R_Axial_DIN0207_L6.3mm_D2.5mm_P7.62mm_Horizontal
SW0, SW1, SW2, SW3, SW4, SW5, SW6, SW7, SW8, SW9, SW10, SW11, SW12, SW13, SW14, SW15, SW16, SW17, SW18, SW19, SW20, SW21, SW22, SW23, SW24: SW_Push; SW_MX

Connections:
/Column0: B0.13 (*10), D0.2 (A), D10.2 (A), D20.2 (A), D30.2 (A), D40.2 (A)
/Column1: B0.14 (11(MOSI)), D2.2 (A), D12.2 (A), D22.2 (A), D32.2 (A), D42.2 (A)
/Column2: B0.15 (12(MISO)), D4.2 (A), D14.2 (A), D24.2 (A), D34.2 (A), D44.2 (A)
/Column3: B0.16 (13(SCK)), D6.2 (A), D16.2 (A), D26.2 (A), D36.2 (A), D46.2 (A)
/Column4: B0.17 (A0), D8.2 (A), D18.2 (A), D28.2 (A), D38.2 (A), D48.2 (A)
/Encoder0ACW: B0.7 (4), ENC0.A
/Encoder0CW: B0.6 (*3), ENC0.B
/Encoder0SW: B0.5 (2), ENC0.S1
/Encoder1ACW: B0.18 (A1), ENC1.A
/Encoder1CW: B0.19 (A2), ENC1.B
/Encoder1SW: B0.20 (A3), ENC1.S1
/Row0: B0.12 (*9), SW0.1, SW1.1, SW2.1, SW3.1, SW4.1
/Row1: B0.11 (8), SW5.1, SW6.1, SW7.1, SW8.1, SW9.1
/Row2: B0.10 (7), SW10.1, SW11.1, SW12.1, SW13.1, SW14.1
/Row3: B0.9 (*6), SW15.1, SW16.1, SW17.1, SW18.1, SW19.1
/Row4: B0.8 (*5), SW20.1, SW21.1, SW22.1, SW23.1, SW24.1
GND: B0.3 (GND), B0.4 (GND), B0.23 (GND), D1.1 (K), D3.1 (K), D5.1 (K), D7.1 (K), D9.1 (K), D11.1 (K), D13.1 (K), D15.1 (K), D17.1 (K), D19.1 (K), D21.1 (K), D23.1 (K), D25.1 (K), D27.1 (K), D29.1 (K), D31.1 (K), D33.1 (K), D35.1 (K), D37.1 (K), D39.1 (K), D41.1 (K), D43.1 (K), D45.1 (K), D47.1 (K), D49.1 (K), ENC0.C, ENC0.S2, ENC1.C, ENC1.S2
unnamed: D0.1 (K), SW0.2
unnamed: D1.2 (A), R0.2
unnamed: D2.1 (K), SW1.2
unnamed: D3.2 (A), R1.2
unnamed: D4.1 (K), SW2.2
unnamed: D5.2 (A), R2.2
unnamed: D6.1 (K), SW3.2
unnamed: D7.2 (A), R3.2
unnamed: D8.1 (K), SW4.2
unnamed: D9.2 (A), R4.2
unnamed: D10.1 (K), SW5.2
unnamed: D11.2 (A), R5.2
unnamed: D12.1 (K), SW6.2
unnamed: D13.2 (A), R6.2
unnamed: D14.1 (K), SW7.2
unnamed: D15.2 (A), R7.2
unnamed: D16.1 (K), SW8.2
unnamed: D17.2 (A), R8.2
unnamed: D18.1 (K), SW9.2
unnamed: D19.2 (A), R9.2
unnamed: D20.1 (K), SW10.2
unnamed: D21.2 (A), R10.2
unnamed: D22.1 (K), SW11.2
unnamed: D23.2 (A), R11.2
unnamed: D24.1 (K), SW12.2
unnamed: D25.2 (A), R12.2
unnamed: D26.1 (K), SW13.2
unnamed: D27.2 (A), R13.2
unnamed: D28.1 (K), SW14.2
unnamed: D29.2 (A), R14.2
unnamed: D30.1 (K), SW15.2
unnamed: D31.2 (A), R15.2
unnamed: D32.1 (K), SW16.2
unnamed: D33.2 (A), R16.2
unnamed: D34.1 (K), SW17.2
unnamed: D35.2 (A), R17.2
unnamed: D36.1 (K), SW18.2
unnamed: D37.2 (A), R18.2
unnamed: D38.1 (K), SW19.2
unnamed: D39.2 (A), R19.2
unnamed: D40.1 (K), SW20.2
unnamed: D41.2 (A), R20.2
unnamed: D42.1 (K), SW21.2
unnamed: D43.2 (A), R21.2
unnamed: D44.1 (K), SW22.2
unnamed: D45.2 (A), R22.2
unnamed: D46.1 (K), SW23.2
unnamed: D47.2 (A), R23.2
unnamed: D48.1 (K), SW24.2
unnamed: D49.2 (A), R24.2
VCC: B0.21 (VCC), R0.1, R1.1, R2.1, R3.1, R4.1, R5.1, R6.1, R7.1, R8.1, R9.1, R10.1, R11.1, R12.1, R13.1, R14.1, R15.1, R16.1, R17.1, R18.1, R19.1, R20.1, R21.1, R22.1, R23.1, R24.1
